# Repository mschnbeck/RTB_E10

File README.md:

# RTB_E10

This E10 module implements a 16 channel WS2811 emulator with compatible bus timing. The E10 may be cascaded with regular WS28xx chips. The number of LEDs is auto detected/configured (0-16). Optionally, the common LED voltage can be controlled over the bus as well.

<details>
<summary>See also</summary>

- [RTB_E13](/../../../../git4dcc/RTB_E13)
- [RTB_E15](/../../../../git4dcc/RTB_E15)

</details>

<details>
<summary>User Guides</summary>

- [User Guide - DE](https://rtb4dcc.de/ws2811_guide_de/)
- User Guide - EN

</details>

The decoder has the following features,
- **Protocol**
  - WS2811 compatible timing
- **LED ports**
  - 0..16 channel output (auto detecting)
  - Software selectable common LED voltage (0 .. 5V)
  - Push/Pull output and can drive common anode or cathode
  - 256 step PWM (240Hz)
  - gamma correction (optional)
- firmware update via V24 debug interface

# Hardware
My current PCB layout uses SMD footprints with 0.5mm pitch and 0603 parts. Reflow soldering is my recommendation, but with some experience handsoldering is also possible.

The hardware allows either push or pull operation. Currently only the pull operation is implemented in the firmware. Should a usecase for push-operation arise, the firmware could be adapted.

## PCB

- 2-layer PCB, FR4, 1.6mm
- CPU: AVR64DA32
- BUS: WS28xx
- LED: Push/Pull

## Kicad
[Schematic](doc/E10_schematic.pdf) | [Layout](doc/E10_layout.pdf) | [Gerber](gerber)

<details>
<summary>Dependency</summary>
<br>

:yellow_circle: Requires my Kicad project library [RTB_SamacSys](/../../../../git4dcc/RTB_SamacSys) in the same directory tree.

</details>

## Firmware
Filename structure: { **pcb** }{ **code** }{ **version** }.hex

Example: **E10F0001**.hex

|   | Description |
| --- | --- |
| **pcb** | Name of matching hardware (**E10**) |
| **code** | Type of code contained (**R**=rom, **B**=bootloader, **F**=flash, **U**=bld update, **P**=UPDI factory code) |
| **version** | Release version (**####**) |

[Firmware files](firmware)

## UPDI
The fuse settings as well as the P-code (E10Pxxxx.hex) has to be installed by using UPDI.<br>

<details>
<summary>Details</summary>

| Fuse Setting | P-Code Install |
| --- | --- |
|||

</details>

## Debug Interface
Subsequent code updates can be done via the built-in serial debug interface.<br>

<details>
<summary>Details</summary>

- connect the serial cable **(1Mb, 8N1, RTS/CTS)**
- press 'break' within the VT100 terminal to bump the module to console prompt
- upload the firmware file (E10Fxxxx.hex)
- for more details, refer to the 'User Guide'

</details>

# Software
The LED common voltage must be sent as the first byte (virtual LED) over the bus followed by the intensity values for the individual LEDs.

```
Byte order:     {voltage} {led_0} ... {led_n}      //'n' being the number of configured LEDs
Led Voltage:    5V * {voltage} / 255
```

# Images

This project is intended for hobby use only and is distributed in accordance with the Apache License 2.0 agreement.

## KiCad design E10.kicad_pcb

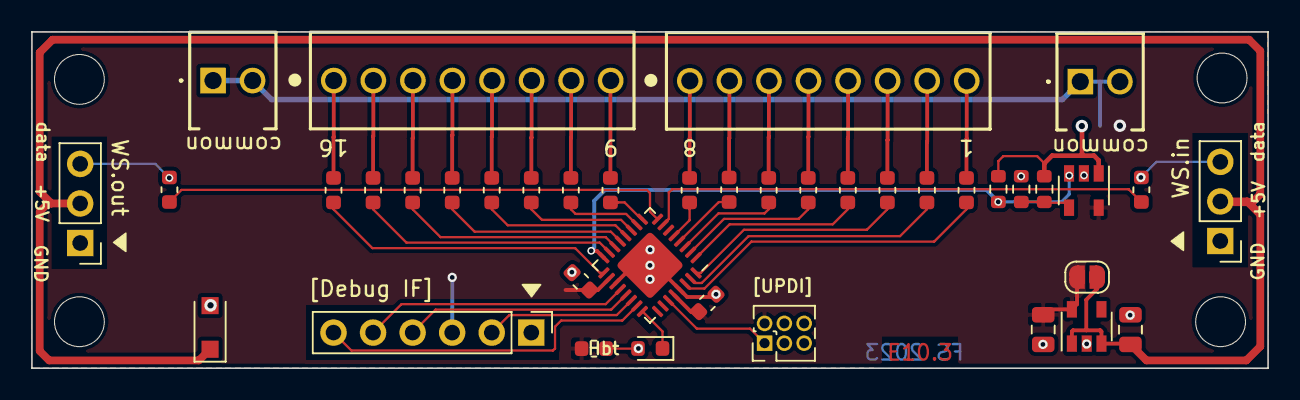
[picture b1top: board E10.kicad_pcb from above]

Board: 2 copper layers, 79.4 x 21.6 mm, 45 parts (1 on the bottom side), 50 nets.

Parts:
C1, C4: 4.7u/10V; C_0805_2012Metric
C2, C3: 100n; C_0603_1608Metric
D1: SS34F; D_SOD-123F
D2: HBT(green); LED_0603_1608Metric
H1, H2, H3, H4: MountingHole; MountingHole_3.2mm_M3_DIN965
J1: LED 8-15; 1725711
J2: WS-bus output; PinHeader_1x03_P2.54mm_Vertical
J3: WS-bus input; PinHeader_1x03_P2.54mm_Vertical
J4: UPDI; PinHeader_2x03_P1.27mm_Vertical
J5: Debug; PinHeader_1x06_P2.54mm_Vertical
J6: LED common; 1725656
J7: LED 0-7; 1725711
J8: LED Common; 1725656
JP1: SolderJumper_2_Open; SolderJumper-2_P1.3mm_Open_RoundedPad1.0x1.5mm
JP2: SolderJumper_3_Open; SolderJumper-3_P1.3mm_Open_RoundedPad1.0x1.5mm
R2, R3, R4, R5, R6, R7, R8, R9, R10, R11, R12, R13, R14, R15, R16, R17: 220; R_0603_1608Metric
R18, R19: 160; R_0603_1608Metric
R20: 4.7k; R_0603_1608Metric
R23: 22; R_0603_1608Metric
R24, R25: 47k; R_0603_1608Metric
U1: AVR-64da32; QFN-32-1EP_5x5mm_P0.5mm_EP3.1x3.1mm
U2: MIC5205-5.0YM5; SOT-23-5
U3: MCP6001; SOT-23-5

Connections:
+5V: C1.1, D1.1, J2.2, J3.2, JP1.1, U2.1, U2.3
DAC: R23.2, U1.16, U3.3
DI: J3.3, R18.2
DO: J2.3, R19.2
GND: C1.2, C2.2, C3.2, C4.2, D1.2, J2.1, J3.1, J4.6, J5.1, R25.2, U1.19, U1.29, U1.33, U2.2, U3.2
unnamed: D2.1, U1.24
unnamed: D2.2, R20.1
unnamed: JP2.1, R23.1, R24.2, U3.1
unnamed: R2.1, U1.13
unnamed: R3.1, U1.14
unnamed: R4.1, U1.15
unnamed: R5.1, U1.17
unnamed: R6.1, U1.9
unnamed: R7.1, U1.10
unnamed: R8.1, U1.11
unnamed: R9.1, U1.12
unnamed: R10.1, U1.2
unnamed: R11.1, U1.3
unnamed: R12.1, U1.4
unnamed: R13.1, U1.5
unnamed: R14.1, U1.30
unnamed: R15.1, U1.31
unnamed: R16.1, U1.32
unnamed: R17.1, U1.1
unnamed: R18.1, U1.7
unnamed: R19.1, U1.8
unnamed: R24.1, R25.1, U3.4
OUT0: J7.8, R14.2
OUT1: J7.7, R15.2
OUT2: J7.6, R16.2
OUT3: J7.5, R17.2
OUT4: J7.4, R10.2
OUT5: J7.3, R11.2
OUT6: J7.2, R12.2
OUT7: J7.1, R13.2
OUT8: J1.8, R6.2
OUT9: J1.7, R7.2
OUT10: J1.6, R8.2
OUT11: J1.5, R9.2
OUT12: J1.4, R2.2
OUT13: J1.3, R3.2
OUT14: J1.2, R4.2
OUT15: J1.1, R5.2
UPDI: J4.1, U1.27
V24.cts: J5.6, U1.23
V24.rts: J5.2, U1.22
V24.rx: J5.4, U1.21
V24.tx: J5.5, U1.20
VDD: C2.1, C3.1, C4.1, J4.2, J5.3, JP1.2, JP2.3, R20.2, U1.18, U1.28, U2.5, U3.5
vCommon: J6.1, J6.2, J8.1, J8.2, JP2.2

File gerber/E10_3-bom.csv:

Value,Designator,Footprint,JLCPCB Part#,Description
Value,Designator,Footprint,JLCPCB Part#,Description
4.7u/10V,"C1,C4",Capacitor_SMD:C_0805_2012Metric,C1779,25V 4.7uF X5R ñ10% 0805 Multilayer Ceramic Capacitors MLCC - SMD/SMT ROHS
100n,"C2,C3",Capacitor_SMD:C_0603_1608Metric,C14663,100nF 50V X7R ñ10% 0603 Multilayer Ceramic Capacitors MLCC - SMD/SMT ROHS
SS34F,D1,Diode_SMD:D_SOD-123F,C719833,-55?~+125? 3A 40V 500mV@3A 500uA@40V 80A Independent SOD-123FL Schottky Diodes ROHS
150,"R18,R19",Resistor_SMD:R_0603_1608Metric,C22808,100mW 150ê 75V Thick Film Resistor ñ1%
4.7k,R20,Resistor_SMD:R_0603_1608Metric,C23162,100mW 4.7kê 75V Thick Film Resistor ñ1%
22,R23,Resistor_SMD:R_0603_1608Metric,C23345,100mW 22ê 75V Thick Film Resistor ñ1%
47k,"R24,R25",Resistor_SMD:R_0603_1608Metric,C25819,100mW 47kê 75V Thick Film Resistor ñ1%
220,"R2,R3,R4,R5,R6,R7,R8,R9,R10,R11,R12,R13,R14,R15,R16,R17",Resistor_SMD:R_0603_1608Metric,C22962,100mW 220ê 75V Thick Film Resistor ñ1%
AVR-64da32,U1,Package_DFN_QFN:QFN-32-1EP_5x5mm_P0.5mm_EP3.1x3.1mm,C3225675,AVR64DA32T-E/RXB
MIC5205-5.0YM5,U2,Package_TO_SOT_SMD:SOT-23-5,C7473162,"-40?~+125?@(Tj) 1 150mA 180mV@(50mA) 20V 2uA 5V 70dB@(1kHz) Fixed Over Current Protection Positive SOT-23-5 Voltage Regulators - Linear, Low Drop Out (LDO) Regulators ROHS"
MCP6001,U3,Package_TO_SOT_SMD:SOT-23-5,C116490,"-40?~+85? 1.0 1.8V~6V 100uA 1MHz 1pA 1pA 23mA 28nV/ûHz@1kHz 2uV/? 4.5mV 600V/ms 6V 76dB Rail-to-Rail Input, Rail-to-Rail Output SOT-23-5 Operational Amplifier ROHS"
HBT(green),D2,LED_SMD:LED_0603_1608Metric,C84264,1.6V~2.6V 13mcd 140ø 25mA 565nm~578nm 576nm 65mW Yellow Green 0603 LED

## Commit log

2025-09-06 mod: optimized for PCB assembly
2026-02-20 Update links in README.md to relative paths
2026-02-20 git mirror test

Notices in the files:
E10.kicad_pcb:
Licensed under the Apache License, Version 2
